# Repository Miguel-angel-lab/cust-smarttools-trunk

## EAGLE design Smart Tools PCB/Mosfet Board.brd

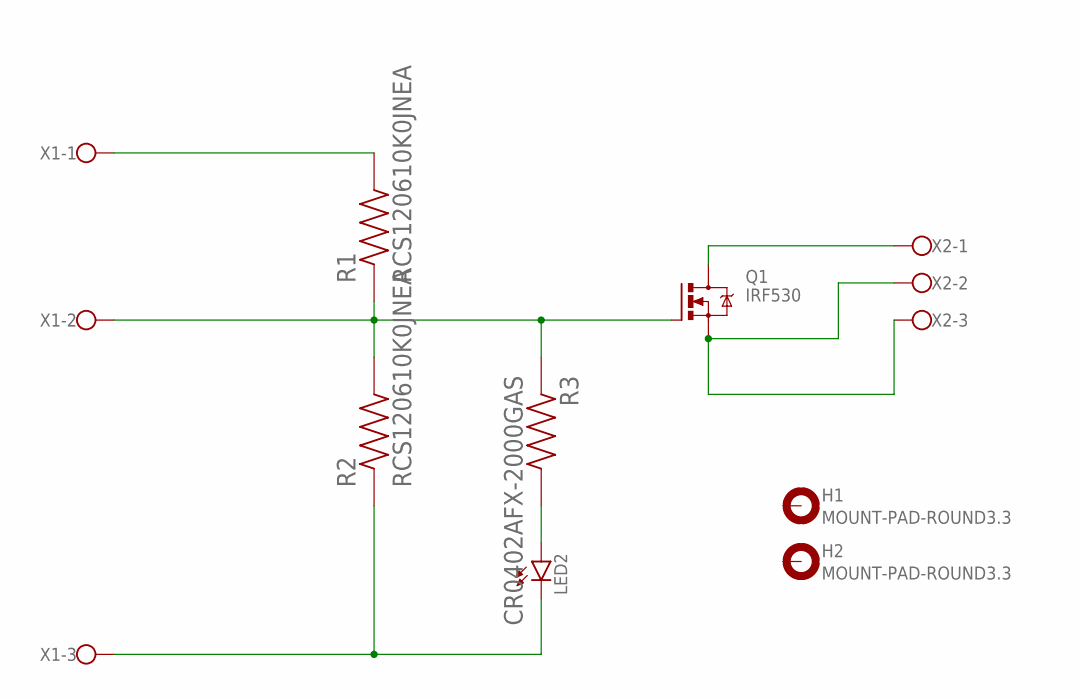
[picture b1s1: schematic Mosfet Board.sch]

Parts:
H1, H2: MOUNT-PAD-ROUND3.3; 3,3-PAD
LED2: LED; SMARTLED-TTW
Q1: IRF530; TO220BV
R1, R2: RCS120610K0JNEA; RESC3116X65N
R3: CR0402AFX-2000GAS; RESC1005X37N
X1, X2: W237-103

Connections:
unnamed: Q1.D, X2.1
unnamed: Q1.S, X2.2, X2.3
unnamed: Q1.G, R1.1, R2.2, R3.1, X1.2
unnamed: LED2.C@1 (C), R2.1, X1.3
unnamed: R1.2, X1.1
unnamed: LED2.A@1 (A), R3.2

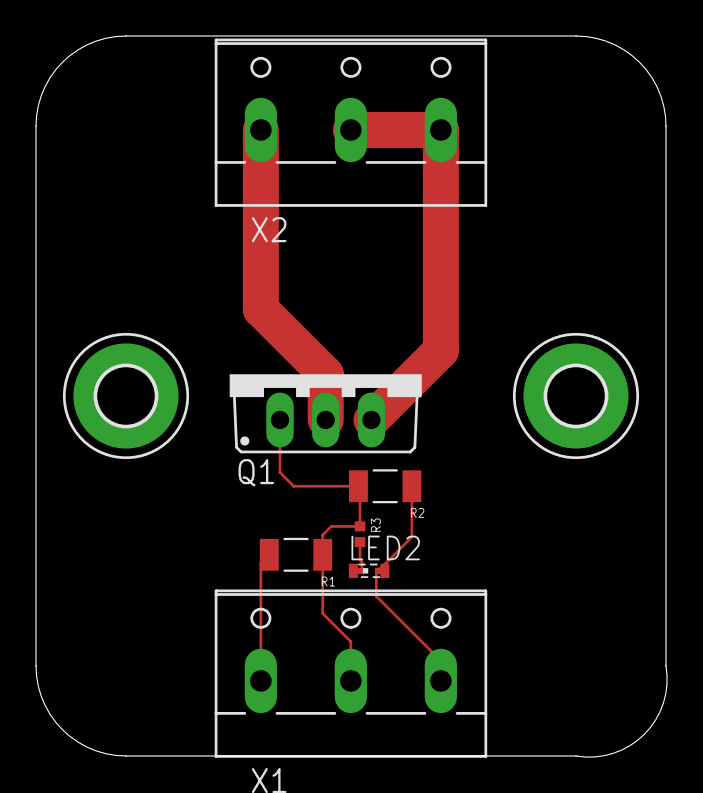
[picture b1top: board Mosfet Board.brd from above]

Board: 2 copper layers, 35.1 x 40.1 mm, 9 parts (0 on the bottom side), 6 nets.

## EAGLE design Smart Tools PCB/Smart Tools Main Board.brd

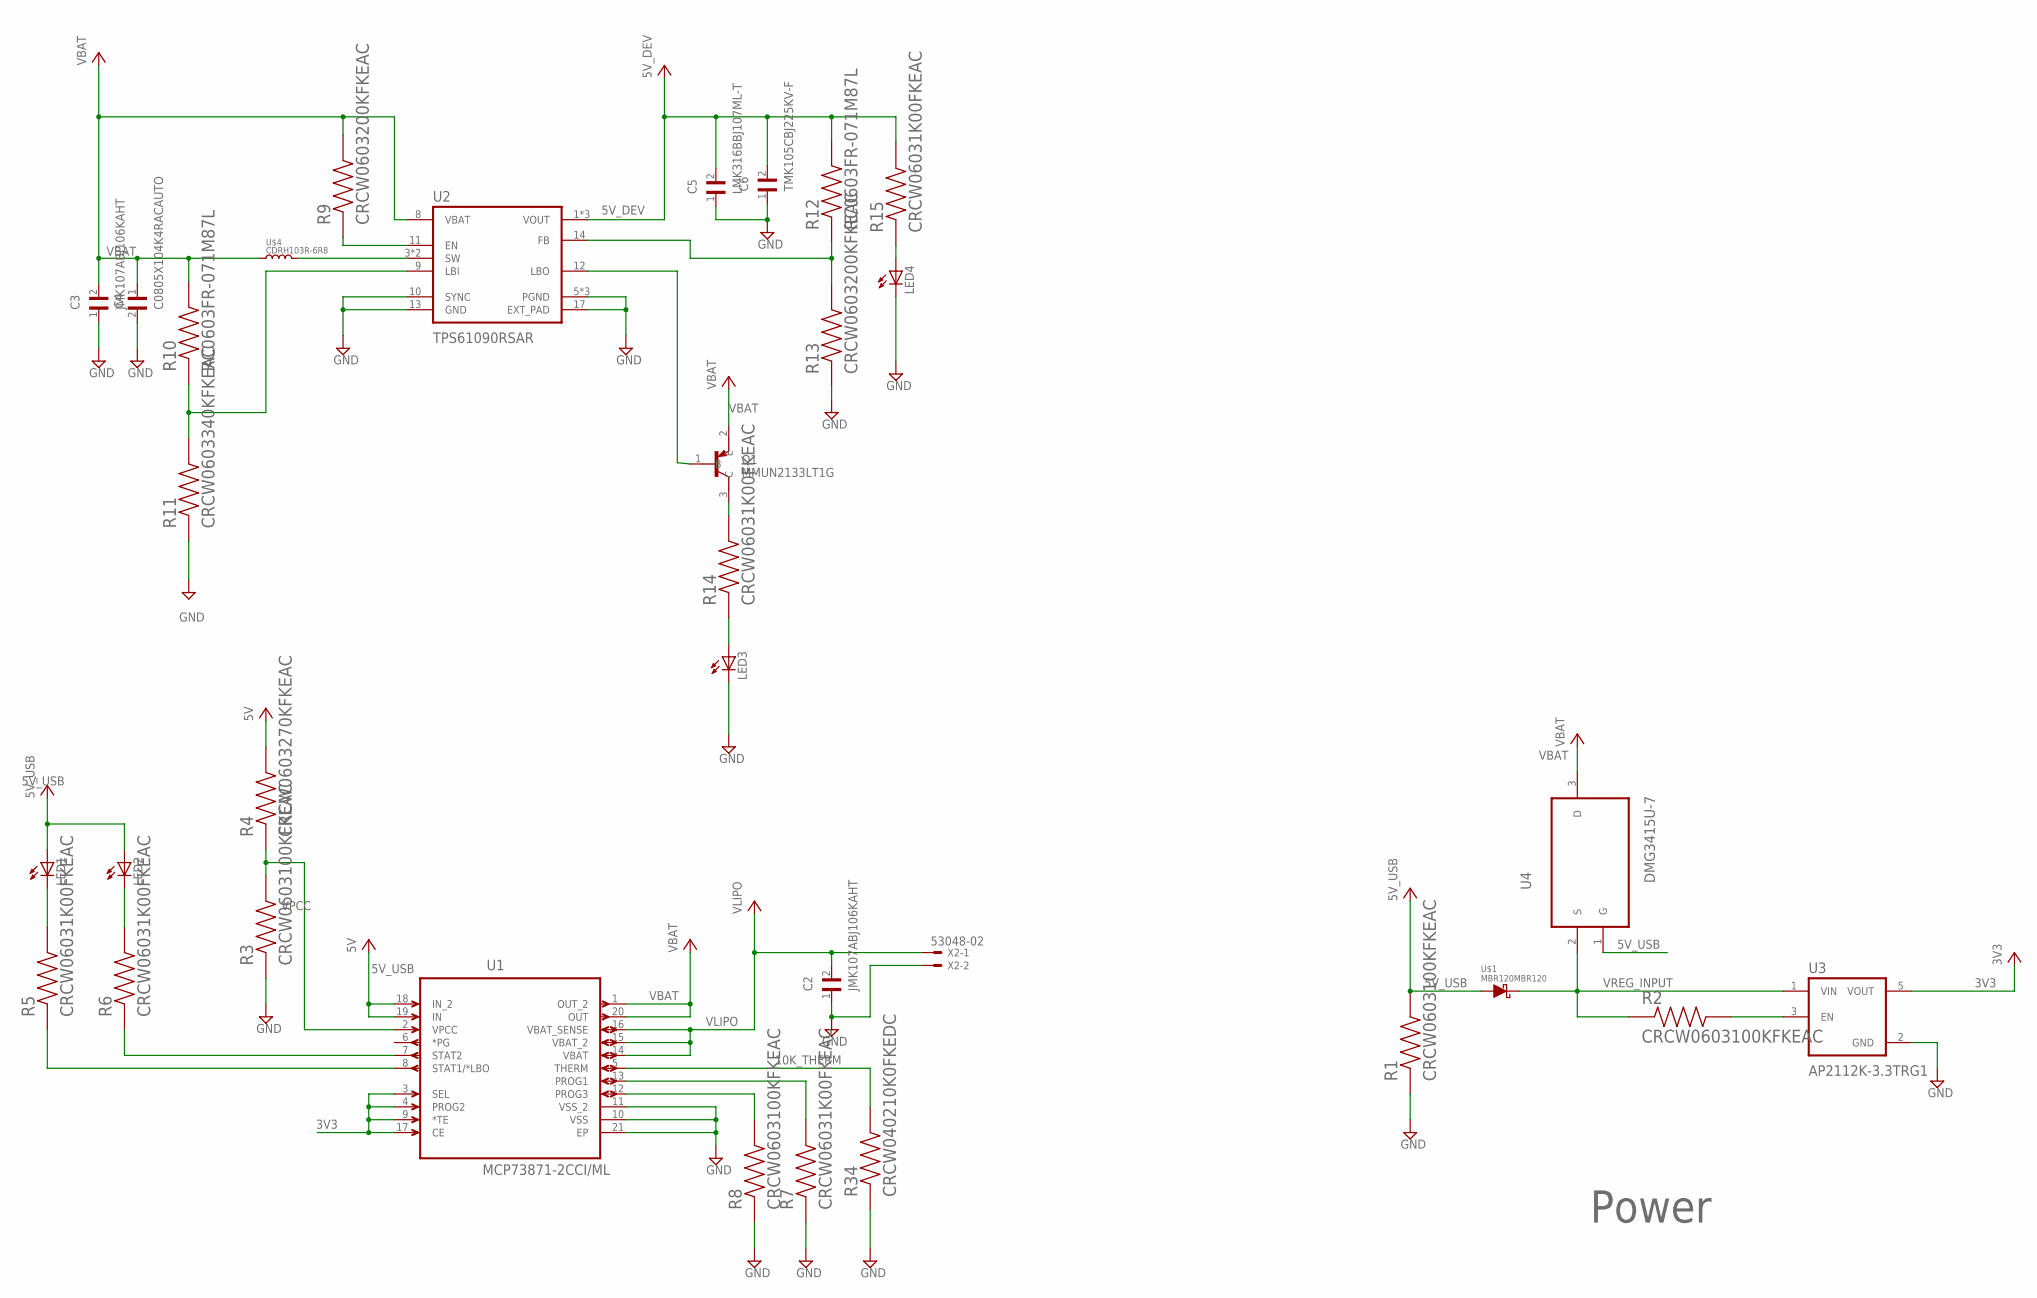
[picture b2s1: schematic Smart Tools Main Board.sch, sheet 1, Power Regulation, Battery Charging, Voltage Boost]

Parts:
C2, C3: JMK107ABJ106KAHT; CAPC1608X95N
C4: C0805X104K4RACAUTO; CAPC2012X88N
C5: LMK316BBJ107ML-T; CAPC3216X190N
C6: TMK105CBJ225KV-F; CAPC1005X70N
LED1, LED2, LED3, LED4: LED_ESML0603; LED_SML0603
Q1: MMUN2133LT1G; SOT95P240X111-3N
R1, R2, R3, R8: CRCW0603100KFKEAC; RESC1608X55N
R4: CRCW0603270KFKEAC; RESC1608X55N
R5, R6, R7, R14, R15: CRCW06031K00FKEAC; RESC1608X55N
R9, R13: CRCW0603200KFKEAC; RESC1608X55N
R10, R12: RC0603FR-071M87L; RESC1608X55N
R11: CRCW0603340KFKEAC; RESC1608X55N
R34: CRCW040210K0FKEDC; RESC1005X35N
U1: MCP73871-2CCI/ML; QFN50P400X400X100-21N
U2: TPS61090RSAR; QFN65P400X400X100-17N
U3: AP2112K-3.3TRG1; SOT95P285X140-5N
U4: DMG3415U-7; SOT95P240X105-3N
U$1: MBR120MBR120; SODFL3616X98N
U$4: CDRH103R-6R8
X2: 53048-02

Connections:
3V3: U1.3 (SEL), U1.4 (PROG2), U1.9 (*TE), U1.17 (CE), U3.5 (VOUT); also elsewhere on the board
5V_DEV: C5.2, C6.2, R12.2, R15.2, U2.1 (VOUT), U2.15 (VOUT), U2.16 (VOUT); also elsewhere on the board
5V_USB: LED1.A, LED2.A, R1.2, U1.18 (IN_2), U1.19 (IN), U4.1 (G), U$1.1 (A); also elsewhere on the board
10K_THERM: R34.2, U1.5 (THERM)
EN: R9.1, U2.11 (EN)
FB: R12.1, R13.2, U2.14 (FB)
GND: C2.1, C3.1, C4.2, C5.1, C6.1, LED3.C, LED4.C, R1.1, R3.1, R7.1, R8.1, R11.1, R13.1, R34.1, U1.10 (VSS), U1.11 (VSS_2), U1.21 (EP), U2.5 (PGND), U2.6 (PGND), U2.7 (PGND), U2.10 (SYNC), U2.13 (GND), U2.17 (EXT_PAD), U3.2 (GND), X2.2; also elsewhere on the board
LBI: R10.1, R11.2, U2.9 (LBI)
unnamed: R2.2, U3.3 (EN)
unnamed: R6.1, U1.7 (STAT2)
unnamed: R5.1, U1.8 (STAT1/*LBO)
unnamed: LED1.C, R5.2
unnamed: LED2.C, R6.2
unnamed: R7.2, U1.13 (PROG1)
unnamed: R8.2, U1.12 (PROG3)
unnamed: Q1.1 (B), U2.12 (LBO)
unnamed: Q1.3 (C), R14.2
unnamed: LED3.A, R14.1
unnamed: LED4.A, R15.1
SW: U2.3 (SW), U2.4 (SW), U$4.2
VBAT: C3.2, C4.1, Q1.2 (E), R9.2, R10.2, U1.1 (OUT_2), U1.20 (OUT), U2.8 (VBAT), U4.3 (D), U$4.1; also elsewhere on the board
VLIPO: C2.2, R4.2, U1.14 (VBAT), U1.15 (VBAT_2), U1.16 (VBAT_SENSE), X2.1
VPCC: R3.2, R4.1, U1.2 (VPCC)
VREG_INPUT: R2.1, U3.1 (VIN), U4.2 (S), U$1.2 (C)

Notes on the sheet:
Power

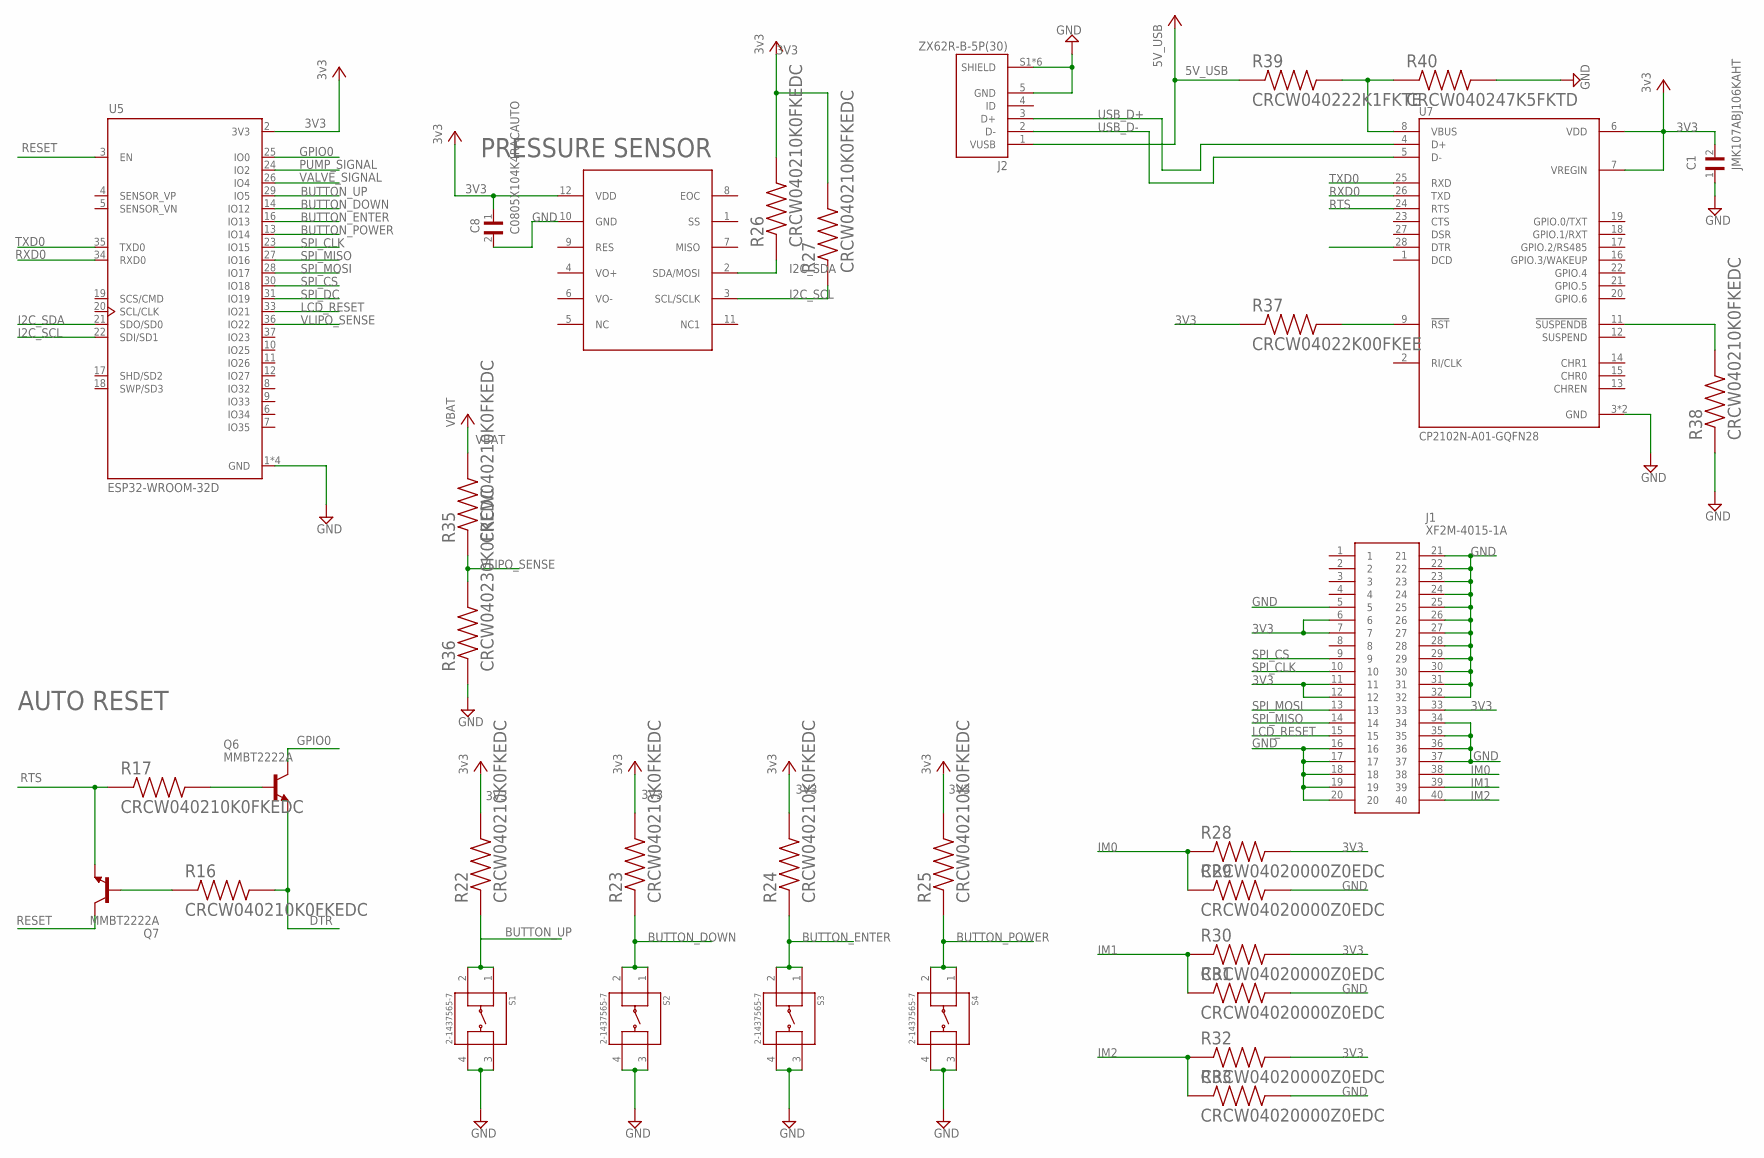
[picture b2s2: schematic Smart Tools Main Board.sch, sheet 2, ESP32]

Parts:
C1: JMK107ABJ106KAHT; CAPC1608X95N
C8: C0805X104K4RACAUTO; CAPC2012X88N
J1: XF2M-4015-1A; XF2M-XX15-1A
J2: ZX62R-B-5P(30); HRS_ZX62R-B-5P(30)
Q6, Q7: MMBT2222A; SOT23
R16, R17, R22, R23, R24, R25, R26, R27, R35, R38: CRCW040210K0FKEDC; RESC1005X35N
R28, R29, R30, R31, R32, R33: CRCW04020000Z0EDC; RESC1005X35N
R36: CRCW040230K0FKEDC; RESC1005X35N
R37: CRCW04022K00FKEE; RESC1005X40N
R39: CRCW040222K1FKTE; RESC1005X40N
R40: CRCW040247K5FKTD; RESC1005X40N
S1, S2, S3, S4: 2-1437565-7; SW_2-1437565-7
U5: ESP32-WROOM-32D; MODULE_ESP32-WROOM-32D
U7: CP2102N-A01-GQFN28; QFN50P500X500X80-29N
U$5: MPRLS0015PG0000SAMPRLS0015PG0000SA; QFN127P500X500X582-12N

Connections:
3V3: C1.2, C8.1, J1.6, J1.7, J1.11, J1.12, J1.33, R22.2, R23.2, R24.2, R25.2, R26.2, R27.2, R28.2, R30.2, R32.2, R37.1, U5.2 (3V3), U7.6 (VDD), U7.7 (VREGIN), U$5.12 (VDD); also elsewhere on the board
5V_USB: J2.1 (VUSB), R39.1; also elsewhere on the board
BUTTON_DOWN: R23.1, S2.1, S2.2, U5.14 (IO12)
BUTTON_ENTER: R24.1, S3.1, S3.2, U5.16 (IO13)
BUTTON_POWER: R25.1, S4.1, S4.2, U5.13 (IO14)
BUTTON_UP: R22.1, S1.1, S1.2, U5.29 (IO5)
DTR: Q6.2 (E), R16.2, U7.28 (DTR)
GND: C1.1, C8.2, J1.5, J1.16, J1.17, J1.18, J1.19, J1.20, J1.21, J1.22, J1.23, J1.24, J1.25, J1.26, J1.27, J1.28, J1.29, J1.30, J1.31, J1.32, J1.34, J1.35, J1.36, J1.37, J2.5 (GND), J2.S1 (SHIELD), J2.S2 (SHIELD), J2.S3 (SHIELD), J2.S4 (SHIELD), J2.S5 (SHIELD), J2.S6 (SHIELD), R29.2, R31.2, R33.2, R36.1, R38.1, R40.2, S1.3, S1.4, S2.3, S2.4, S3.3, S3.4, S4.3, S4.4, U5.1 (GND), U5.15 (GND), U5.38 (GND), U5.39 (GND), U7.3 (GND), U7.29 (GND), U$5.10 (GND); also elsewhere on the board
GPIO0: Q6.3 (C), U5.25 (IO0)
I2C_SCL: R27.1, U5.22 (SDI/SD1), U$5.3 (SCL/SCLK)
I2C_SDA: R26.1, U5.21 (SDO/SD0), U$5.2 (SDA/MOSI)
IM0: J1.38, R28.1, R29.1
IM1: J1.39, R30.1, R31.1
IM2: J1.40, R32.1, R33.1
LCD_RESET: J1.15, U5.33 (IO21)
unnamed: Q7.1 (B), R16.1
unnamed: Q6.1 (B), R17.2
unnamed: R37.2, U7.9 (!RST)
unnamed: R38.2, U7.11 (!SUSPENDB)
unnamed: R39.2, R40.1, U7.8 (VBUS)
PUMP_SIGNAL: U5.24 (IO2); also elsewhere on the board
RESET: Q7.3 (C), U5.3 (EN)
RTS: Q7.2 (E), R17.1, U7.24 (RTS)
RXD0: U5.34 (RXD0), U7.26 (TXD)
SPI_CLK: J1.10, U5.23 (IO15)
SPI_CS: J1.9, U5.30 (IO18)
SPI_DC: U5.31 (IO19)
SPI_MISO: J1.14, U5.27 (IO16)
SPI_MOSI: J1.13, U5.28 (IO17)
TXD0: U5.35 (TXD0), U7.25 (RXD)
USB_D+: J2.3 (D+), U7.4 (D+)
USB_D-: J2.2 (D-), U7.5 (D-)
VALVE_SIGNAL: U5.26 (IO4); also elsewhere on the board
VBAT: R35.2; also elsewhere on the board
VLIPO_SENSE: R35.1, R36.2, U5.36 (IO22)

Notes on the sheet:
AUTO RESET
PRESSURE SENSOR

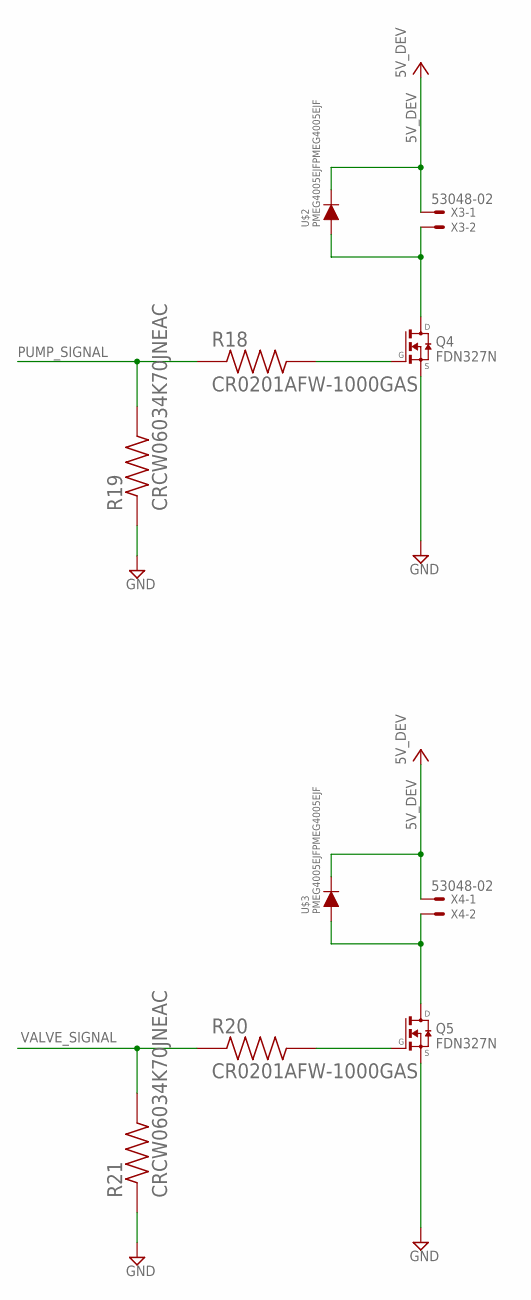
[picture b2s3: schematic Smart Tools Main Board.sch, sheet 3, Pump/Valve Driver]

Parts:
Q4, Q5: FDN327N; SSOT-3
R18, R20: CR0201AFW-1000GAS; RESC0603X26N
R19, R21: CRCW06034K70JNEAC; RESC1608X55N
U$2, U$3: PMEG4005EJFPMEG4005EJF; SOD2512X80N
X3, X4: 53048-02

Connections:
5V_DEV: U$2.2 (C), U$3.2 (C), X3.1, X4.1; also elsewhere on the board
GND: Q4.2 (S), Q5.2 (S), R19.1, R21.1; also elsewhere on the board
unnamed: Q4.1 (G), R18.2
unnamed: Q4.3 (D), U$2.1 (A), X3.2
unnamed: Q5.1 (G), R20.2
unnamed: Q5.3 (D), U$3.1 (A), X4.2
PUMP_SIGNAL: R18.1, R19.2; also elsewhere on the board
VALVE_SIGNAL: R20.1, R21.2; also elsewhere on the board

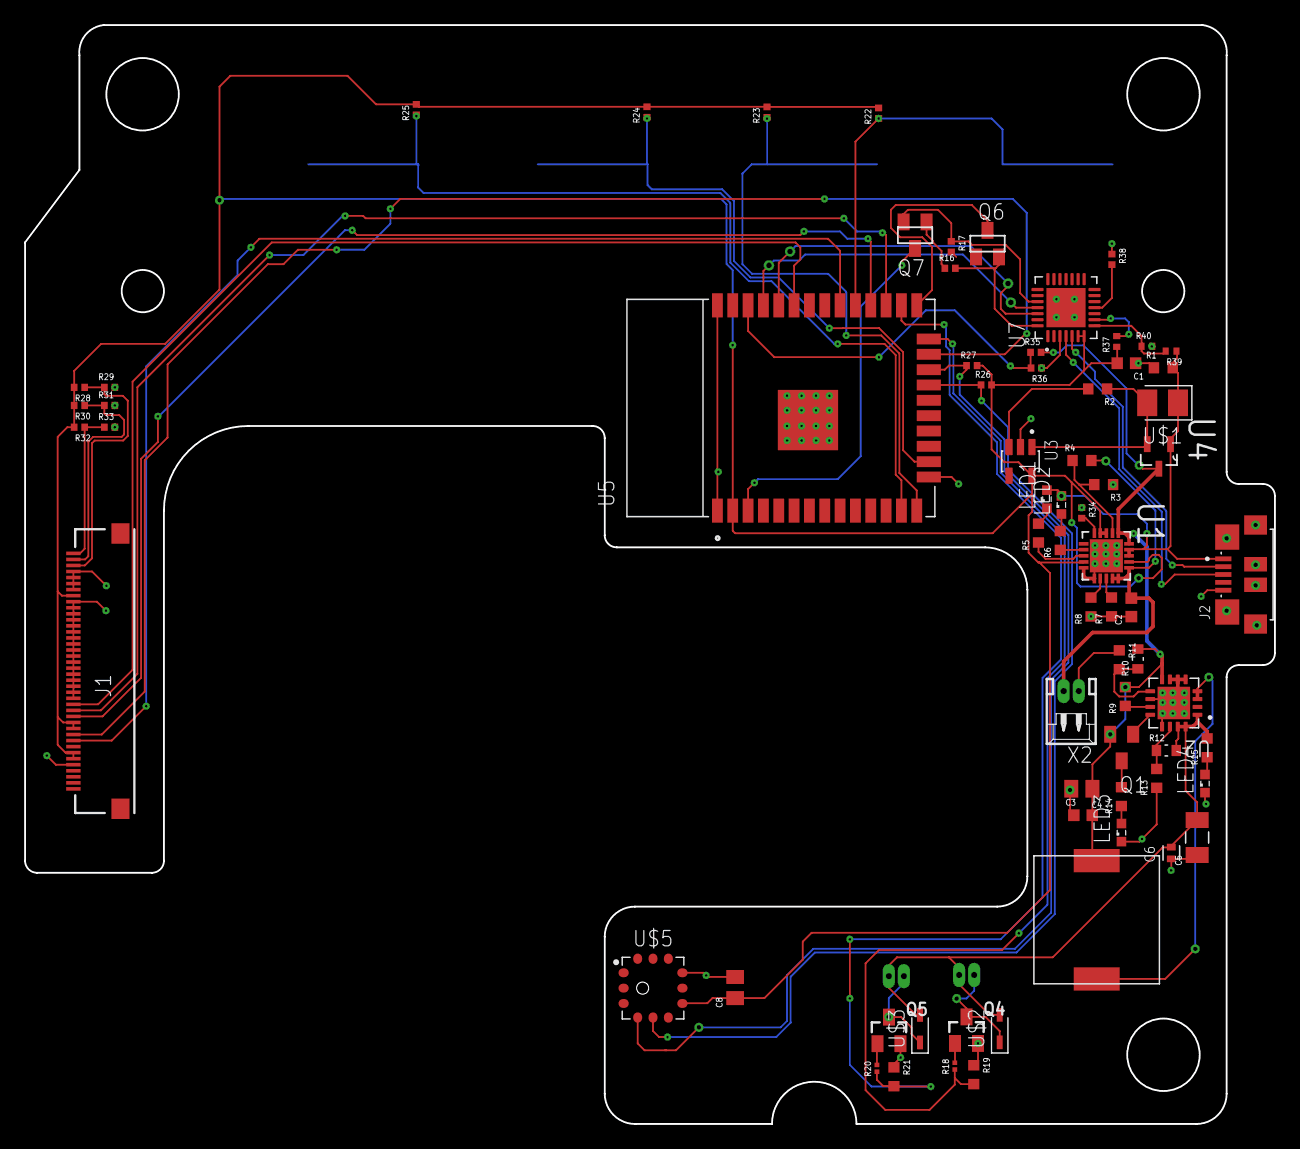
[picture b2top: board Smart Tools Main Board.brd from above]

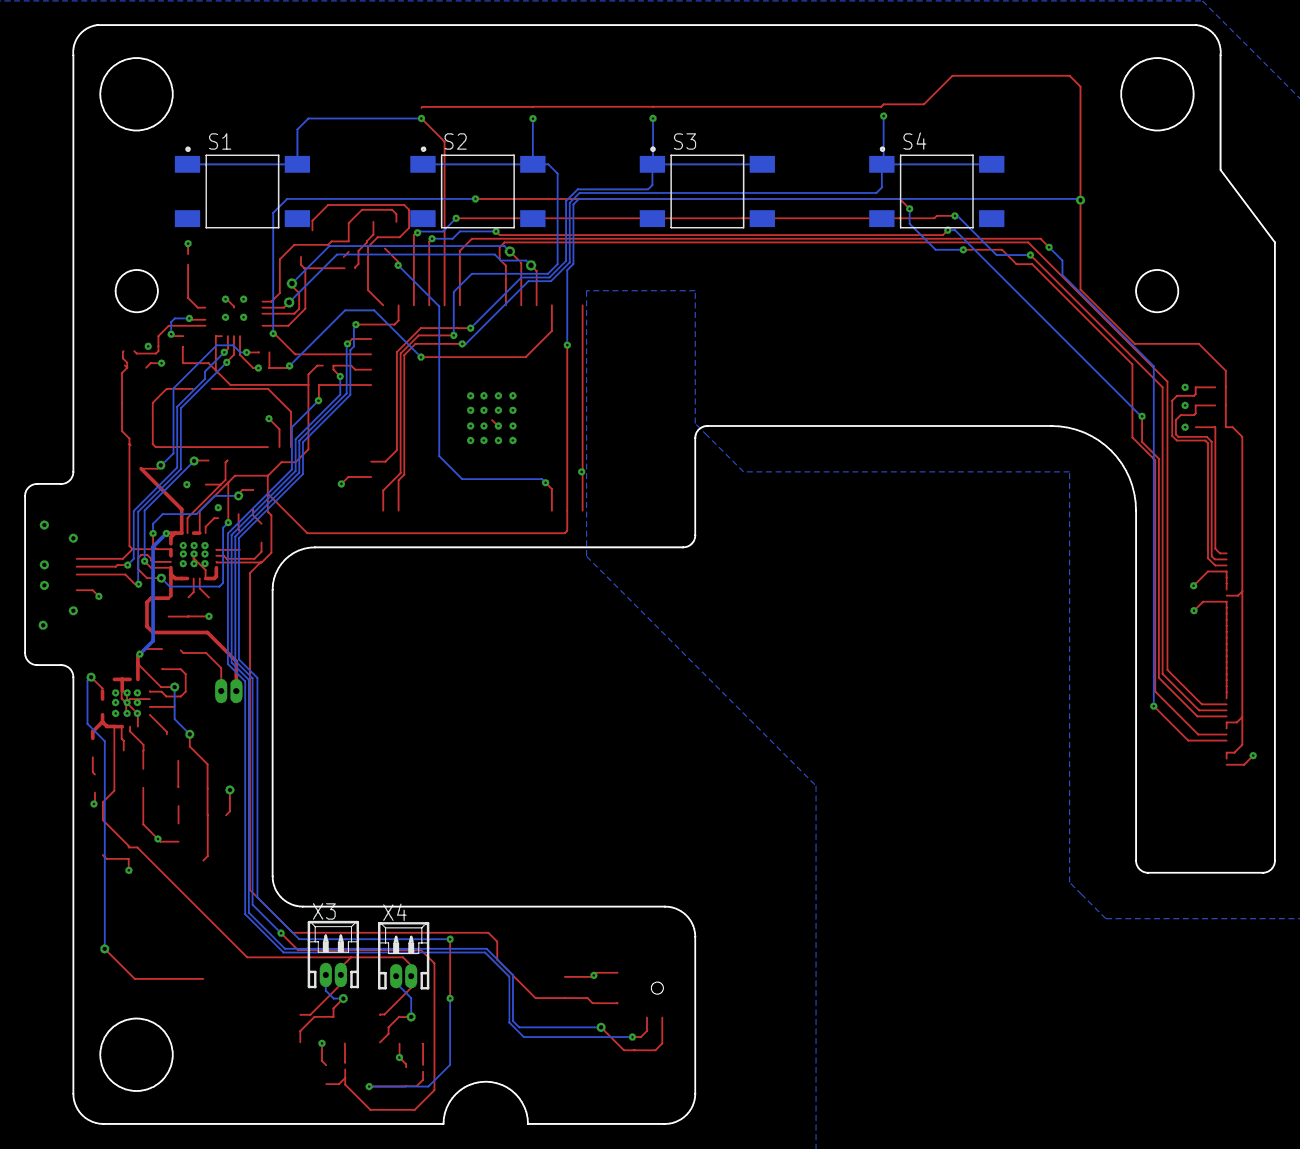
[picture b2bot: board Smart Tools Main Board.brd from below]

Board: 2 copper layers, 103.5 x 91.0 mm, 76 parts (6 on the bottom side), 58 nets.

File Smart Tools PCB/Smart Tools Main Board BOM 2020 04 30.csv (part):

Part,Value,Device,Package,Description,AVAILABILITY,COMMENT,CONFIGURATION_POLE-THROW,CONTACT_CURRENT_RATING,DESCRIPTION,DIGI-KEY_PART_NUMBER,DIGI-KEY_PURCHASE_URL,HEIGHT,MANUFACTURER_NAME,MANUFACTURER_PART_NUMBER,MF,MOUSER_PART_NUMBER,MOUSER_PRICE-STOCK,MP,MPN,OC_FARNELL,OC_NEWARK,PACKAGE,POPULARITY,PRICE,SPICEMODEL,SPICEPREFIX,SPICETYPE,TE_PURCHASE_URL,
C1,JMK107ABJ106KAHT,JMK107ABJ106KAHT,CAPC1608X95N,,Unavailable,,,,0,,,,,,Taiyo Yuden,,,JMK107ABJ106KAHT,,,,1608 Taiyo Yuden,,None,,,,,
C2,JMK107ABJ106KAHT,JMK107ABJ106KAHT,CAPC1608X95N,,Unavailable,,,,0,,,,,,Taiyo Yuden,,,JMK107ABJ106KAHT,,,,1608 Taiyo Yuden,,None,,,,,
C3,JMK107ABJ106KAHT,JMK107ABJ106KAHT,CAPC1608X95N,,Unavailable,,,,0,,,,,,Taiyo Yuden,,,JMK107ABJ106KAHT,,,,1608 Taiyo Yuden,,None,,,,,
C4,C0805X104K4RACAUTO,C0805X104K4RACAUTO,CAPC2012X88N,,Unavailable,,,,CAP CER 0.1UF 16V X7R 0805,,,,,,KEMET,,,C0805X104K4RACAUTO,,,,0805 KEMET,,None,,,,,
C5,LMK316BBJ107ML-T,LMK316BBJ107ML-T,CAPC3216X190N,,Unavailable,,,,"CAP, MLCC, 1206/3216, 10V, X5R,",,,,,,Taiyo Yuden,,,LMK316BBJ107ML-T,,,,3216 Taiyo Yuden,,None,,,,,
C6,TMK105CBJ225KV-F,TMK105CBJ225KV-F,CAPC1005X70N,,Unavailable,,,,CAP CER 2.2UF 25V X5R 0402,,,,,,Taiyo Yuden,,,TMK105CBJ225KV-F,,,,1005 Taiyo Yuden,,None,,,,,
C8,C0805X104K4RACAUTO,C0805X104K4RACAUTO,CAPC2012X88N,,Unavailable,,,,CAP CER 0.1UF 16V X7R 0805,,,,,,KEMET,,,C0805X104K4RACAUTO,,,,0805 KEMET,,None,,,,,
J1,XF2M-4015-1A,XF2M-4015-1A,XF2M-XX15-1A,Omron XF2M Series 0.5mm Pitch 40 Way 1 Row Right Angle SMT Female FPC Connector Locking Mechanism,,,,,Omron XF2M Series 0.5mm Pitch 40 Way 1 Row Right Angle SMT Female FPC Connector Locking Mechanism,,,mm,Omron Electronics,XF2M-4015-1A,,653-XF2M-4015-1A,https://www.mouser.com/Search/Refine.aspx?Keyword=653-XF2M-4015-1A,,,,,,,,,,,,
J2,ZX62R-B-5P(30),ZX62R-B-5P(30),HRS_ZX62R-B-5P(30),ZX Series 5 Pin Single Port USB 2.0 Micro B Top Mount Receptacle Male,Unavailable,,,,"USB - micro B USB 2.0 Receptacle Connector 5 Position Surface Mount, Right Angle",,,,,,Hirose,,,ZX62R-B-5P_30_,,,,None,,None,,,,,
LED1,,LED_ESML0603,LED_SML0603,LED,,,,,,,,,,,,,,,,,,,,,NONE,D,diode,,
LED2,,LED_ESML0603,LED_SML0603,LED,,,,,,,,,,,,,,,,,,,,,NONE,D,diode,,
LED3,,LED_ESML0603,LED_SML0603,LED,,,,,,,,,,,,,,,,,,,,,NONE,D,diode,,
LED4,,LED_ESML0603,LED_SML0603,LED,,,,,,,,,,,,,,,,,,,,,NONE,D,diode,,
Q1,MMUN2133LT1G,MMUN2133LT1G,SOT95P240X111-3N,Bias Resistor Transistors PNP Silicon SM Transistors with Monolithic Bias Resistor Network,Unavailable,,,, Bias Resistor Transistors PNP Silicon SM Transistors with Monolithic Bias Resistor Network ,,,,,,ON Semiconductor,,,MMUN2133LT1G,,,,SOT-23-3 ON Semiconductor,,None,,,,,
Q4,FDN327N,FDN327N,SSOT-3,N-Channel MOSFET,Unavailable,,,,N-Channel 20V 70 mOhm 1.8 V Specified PowerTrench Mosfet - SSOT-3,,,,,,ON Semiconductor,,,FDN327N,,,,SC-59 ON Semiconductor,,None,,,,,
Q5,FDN327N,FDN327N,SSOT-3,N-Channel MOSFET,Unavailable,,,,N-Channel 20V 70 mOhm 1.8 V Specified PowerTrench Mosfet - SSOT-3,,,,,,ON Semiconductor,,,FDN327N,,,,SC-59 ON Semiconductor,,None,,,,,
Q6,MMBT2222A,MMBT2222A,SOT23,2N2222 General Purpose NPN Transistor,Unavailable,,,,Bipolar _BJT_ Transistor NPN 40V 600mA 300MHz 310mW Surface Mount SOT-23-3,,,,,,STMicroelectronics,,,MMBT2222A,,,,TO-236-3 Taitron,,None,,,,,
Q7,MMBT2222A,MMBT2222A,SOT23,2N2222 General Purpose NPN Transistor,Unavailable,,,,Bipolar _BJT_ Transistor NPN 40V 600mA 300MHz 310mW Surface Mount SOT-23-3,,,,,,STMicroelectronics,,,MMBT2222A,,,,TO-236-3 Taitron,,None,,,,,
R1,CRCW0603100KFKEAC,CRCW0603100KFKEAC,RESC1608X55N,Res Thick Film 0603 100K Ohm 1% 1/10W Â±100ppm/Â°C Molded SMD Paper T/R,Unavailable,,,,Viscrcw0603100kfkeac Chip Res 0603 100k,,,,,,Vishay Dale,,,CRCW0603100KFKEAC,,,,1608 Rohm Semiconductor,,None,,,,,
R2,CRCW0603100KFKEAC,CRCW0603100KFKEAC,RESC1608X55N,Res Thick Film 0603 100K Ohm 1% 1/10W Â±100ppm/Â°C Molded SMD Paper T/R,Unavailable,,,,Viscrcw0603100kfkeac Chip Res 0603 100k,,,,,,Vishay Dale,,,CRCW0603100KFKEAC,,,,1608 Rohm Semiconductor,,None,,,,,
R3,CRCW0603100KFKEAC,CRCW0603100KFKEAC,RESC1608X55N,Res Thick Film 0603 100K Ohm 1% 1/10W Â±100ppm/Â°C Molded SMD Paper T/R,Unavailable,,,,Viscrcw0603100kfkeac Chip Res 0603 100k,,,,,,Vishay Dale,,,CRCW0603100KFKEAC,,,,1608 Rohm Semiconductor,,None,,,,,
R4,CRCW0603270KFKEAC,CRCW0603270KFKEAC,RESC1608X55N,RES 270K OHM 1% 1/10W 0603,Unavailable,,,,Res Thick Film 0603 270K Ohm 1% 1/10W ±100ppm/°C Molded SMD Paper T/R,,,,,,Vishay,,,CRCW0603270KFKEAC,,,,1608 Rohm Semiconductor,,None,,,,,
R5,CRCW06031K00FKEAC,CRCW06031K00FKEAC,RESC1608X55N,,Unavailable,,,,D11/CRCW0603-C 100 1K0 1% ET1,,,,,,Vishay Dale,,,CRCW06031K00FKEAC,,,,1608 Rohm Semiconductor,,None,,,,,
R6,CRCW06031K00FKEAC,CRCW06031K00FKEAC,RESC1608X55N,,Unavailable,,,,D11/CRCW0603-C 100 1K0 1% ET1,,,,,,Vishay Dale,,,CRCW06031K00FKEAC,,,,1608 Rohm Semiconductor,,None,,,,,
R7,CRCW06031K00FKEAC,CRCW06031K00FKEAC,RESC1608X55N,,Unavailable,,,,D11/CRCW0603-C 100 1K0 1% ET1,,,,,,Vishay Dale,,,CRCW06031K00FKEAC,,,,1608 Rohm Semiconductor,,None,,,,,
R8,CRCW0603100KFKEAC,CRCW0603100KFKEAC,RESC1608X55N,Res Thick Film 0603 100K Ohm 1% 1/10W Â±100ppm/Â°C Molded SMD Paper T/R,Unavailable,,,,Viscrcw0603100kfkeac Chip Res 0603 100k,,,,,,Vishay Dale,,,CRCW0603100KFKEAC,,,,1608 Rohm Semiconductor,,None,,,,,
R9,CRCW0603200KFKEAC,CRCW0603200KFKEAC,RESC1608X55N,,,,,, Standard Thick Film Chip Resistors ,541-4027-1-ND,https://www.digikey.com/product-detail/en/vishay-dale/CRCW06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,,,,Vishay,,,CRCW0603200KFKEAC,,,,1608 Rohm Semiconductor,,,,,,,
R10,RC0603FR-071M87L,RC0603FR-071M87L,RESC1608X55N,RES SMD 1.87M OHM 1% 1/10W 0603,Unavailable,,,,Res Thick Film 0603 1.87M Ohm 1% 0.1W_1/10W_ ±100ppm/C Molded SMD Paper T/R,,,,,,Yageo,,,RC0603FR-071M87L,,,,1608 Yageo,,None,,,,,
R11,CRCW0603340KFKEAC,CRCW0603340KFKEAC,RESC1608X55N,,Unavailable,,,,D11/CRCW0603-C 100 340K 1% ET1,,,,,,Vishay,,,CRCW0603340KFKEAC,,,,1608 Rohm Semiconductor,,None,,,,,
R12,RC0603FR-071M87L,RC0603FR-071M87L,RESC1608X55N,RES SMD 1.87M OHM 1% 1/10W 0603,Unavailable,,,,Res Thick Film 0603 1.87M Ohm 1% 0.1W_1/10W_ ±100ppm/C Molded SMD Paper T/R,,,,,,Yageo,,,RC0603FR-071M87L,,,,1608 Yageo,,None,,,,,
R13,CRCW0603200KFKEAC,CRCW0603200KFKEAC,RESC1608X55N,,,,,, Standard Thick Film Chip Resistors ,541-4027-1-ND,https://www.digikey.com/product-detail/en/vishay-dale/CRCW06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,,,,Vishay,,,CRCW0603200KFKEAC,,,,1608 Rohm Semiconductor,,,,,,,
R14,CRCW06031K00FKEAC,CRCW06031K00FKEAC,RESC1608X55N,,Unavailable,,,,D11/CRCW0603-C 100 1K0 1% ET1,,,,,,Vishay Dale,,,CRCW06031K00FKEAC,,,,1608 Rohm Semiconductor,,None,,,,,
R15,CRCW06031K00FKEAC,CRCW06031K00FKEAC,RESC1608X55N,,Unavailable,,,,D11/CRCW0603-C 100 1K0 1% ET1,,,,,,Vishay Dale,,,CRCW06031K00FKEAC,,,,1608 Rohm Semiconductor,,None,,,,,
R16,CRCW040210K0FKEDC,CRCW040210K0FKEDC,RESC1005X35N,RES SMD 10K OHM 1% 1/16W 0402,Unavailable,,,,Res Thick Film 0402 10K Ohm 1% 1/16W ±100ppm/°C Molded SMD Paper T/R,,,,,,Vishay Dale,,,CRCW040210K0FKEDC,,,,1005 Yageo,,None,,,,,
R17,CRCW040210K0FKEDC,CRCW040210K0FKEDC,RESC1005X35N,RES SMD 10K OHM 1% 1/16W 0402,Unavailable,,,,Res Thick Film 0402 10K Ohm 1% 1/16W ±100ppm/°C Molded SMD Paper T/R,,,,,,Vishay Dale,,,CRCW040210K0FKEDC,,,,1005 Yageo,,None,,,,,
R18,CR0201AFW-1000GAS,CR0201AFW-1000GAS,RESC0603X26N,,Unavailable,,,,ResA-AS 0201 100R 1% 50mW TC200,,,,,,Bourns,,,CR0201AFW-1000GAS,,,,0603 Rohm Semiconductor,,None,,,,,
R19,CRCW06034K70JNEAC,CRCW06034K70JNEAC,RESC1608X55N,,Unavailable,,,,D11/CRCW0603-C 200 4K7 5% ET1,,,,,,Vishay,,,CRCW06034K70JNEAC,,,,1608 Rohm Semiconductor,,None,,,,,
R20,CR0201AFW-1000GAS,CR0201AFW-1000GAS,RESC0603X26N,,Unavailable,,,,ResA-AS 0201 100R 1% 50mW TC200,,,,,,Bourns,,,CR0201AFW-1000GAS,,,,0603 Rohm Semiconductor,,None,,,,,
R21,CRCW06034K70JNEAC,CRCW06034K70JNEAC,RESC1608X55N,,Unavailable,,,,D11/CRCW0603-C 200 4K7 5% ET1,,,,,,Vishay,,,CRCW06034K70JNEAC,,,,1608 Rohm Semiconductor,,None,,,,,
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
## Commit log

2020-09-04 initial commit for estimation
